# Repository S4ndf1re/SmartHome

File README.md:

# SmartHome

During Covid-19 lockdown, I started a hobby project to experiment with plugin support for MQTT Services.
This repository is the result.

Primarily, this project connected MQTT connections and web UI components with plugins written in Java / Kotlin.

To tests the projects validity, an automatic doorlock opener was developed. This doorlock plugin registered into the plugin systems,
exposed its functionality over Websockets and normal HTTP Endpoints, and communicated over MQTT with two ESP8266, one responsible for reading chips, one for actuating the doorlock mechanism.

For roughly one year, this tool in actual use, until [Smart Home V2](https://github.com/S4ndf1re/SmartHomeV2) was developed as its replacement, due to repeating issues with the Eclipse MQTT Client Library.

# Dependencies

- [HiveMQ MQTT Broker community edition](https://github.com/hivemq/hivemq-community-edition)
- [Dokka Documentation Tool for Kotlin](https://github.com/Kotlin/dokka)

# Documenting the code

The code can be documented as following:

```
.\gradlew :lib:dokkaHtml
.\gradlew :backend:dokkaHtml
```

# "Installing"

To use this Smarthome tool, you have to do the following:

1. Make sure to have a reachable MySql database (currently, only MySql is supported)
2. Create on database using the sql_script.sql file.
3. Build using .\gradlew :backend:build
4. Put the generated jar from build/libs into ./
5. Create all plugins in the ./plugins folder.
6. Create all controller in the ./controller folder.

# Plugins

There is only one test plugin to check whether your build works. It can be found in plugin_test

# Controller

There is one default http controller. The controller resembles just an API. In order to use it, you should consider
using the Smarthome_frontend repository.

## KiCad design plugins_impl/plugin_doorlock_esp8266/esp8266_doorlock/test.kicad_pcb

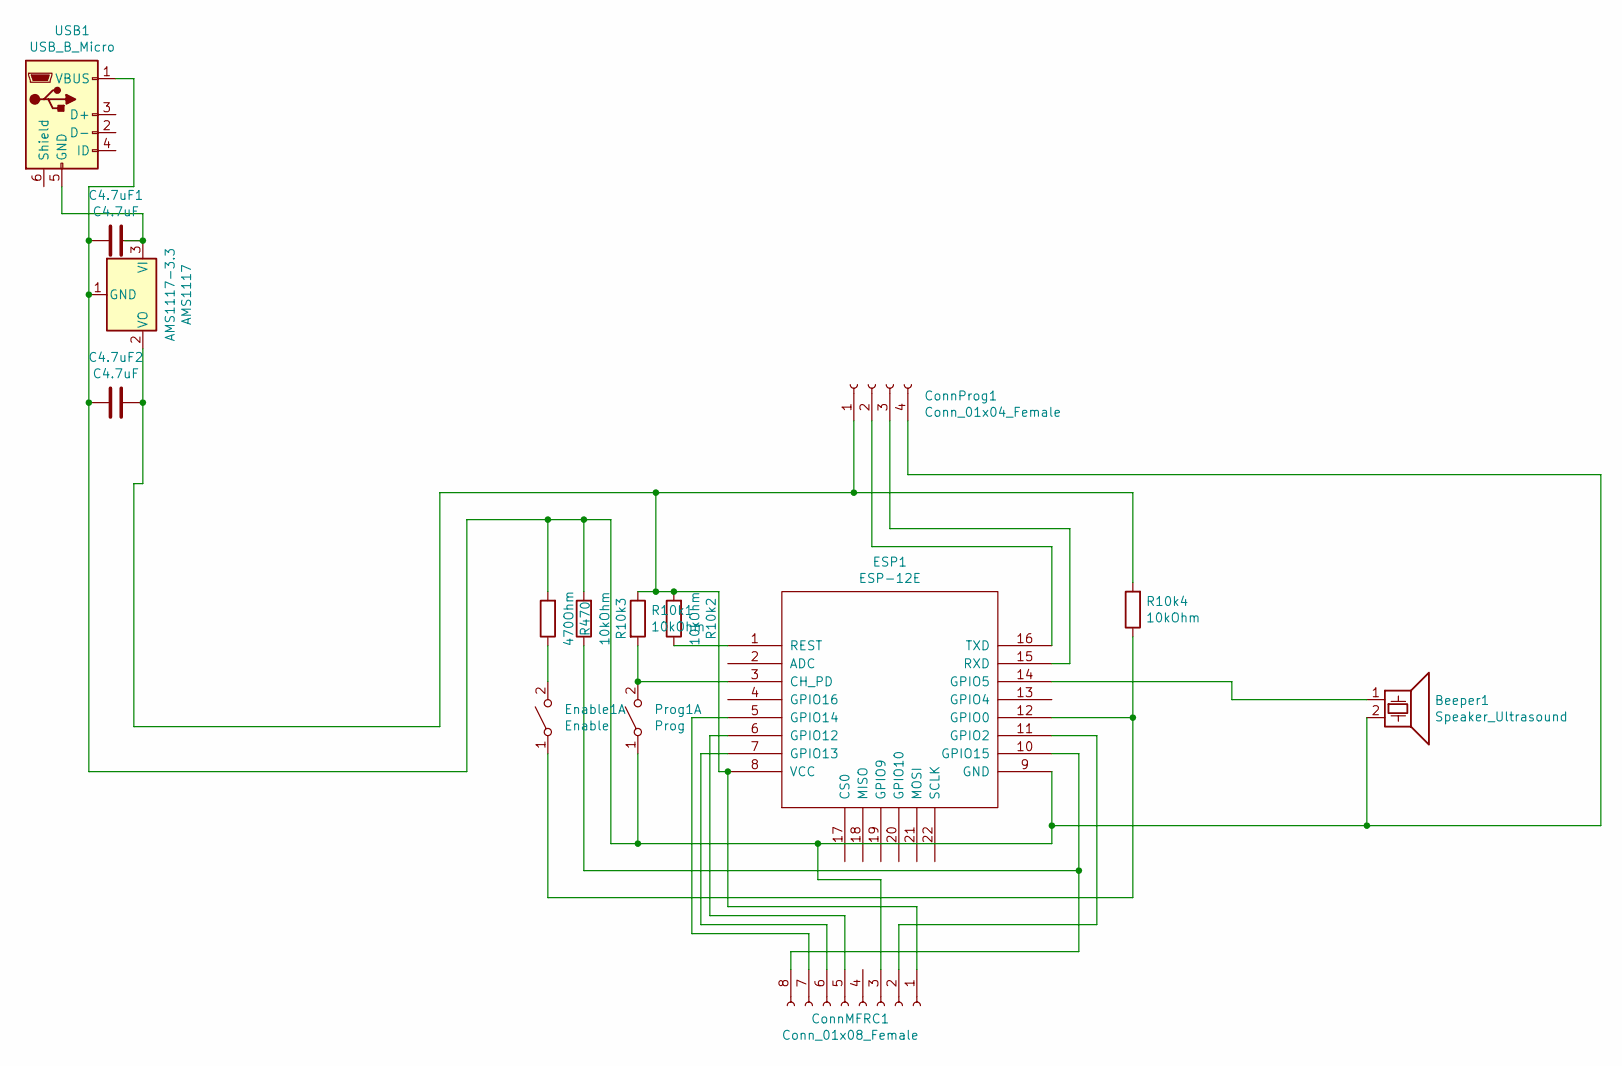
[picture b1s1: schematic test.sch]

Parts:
AMS1117: AMS1117-3.3; SOT-223-3Lead_TabPin2
Beeper1: Speaker_Ultrasound; Buzzer_9mm_6mm
C4.7uF1, C4.7uF2: C4.7uF; CP_Elec_4x5.4
ConnMFRC1: Conn_01x08_Female; MFRC522_PinHeader
ConnProg1: Conn_01x04_Female; TerminalBlock_MetzConnect_Type059_RT06304HBWC_1x04_P3.50mm_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
ESP1: ESP-12E; esp12f
Enable1: Enable; Button
Prog1: Prog; Button
R10k1, R10k2, R10k3, R10k4: 10kOhm; R_0805_2012Metric_Pad1.20x1.40mm_HandSolder
R470: 470Ohm; R_0805_2012Metric_Pad1.20x1.40mm_HandSolder
USB1: USB_B_Micro; USB_Micro-B_Molex-105017-0001

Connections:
unnamed: AMS1117.1 (GND), Beeper1.2, C4.7uF1.2, C4.7uF2.2, ConnMFRC1.3, ConnProg1.4, ESP1.9 (GND), Prog1.1 (A), R10k3.2, R470.2, USB1.1 (VBUS)
unnamed: AMS1117.2 (VO), C4.7uF2.1, ConnMFRC1.1, ConnProg1.1, ESP1.8 (VCC), R10k1.1, R10k2.2, R10k4.2
unnamed: AMS1117.3 (VI), C4.7uF1.1, USB1.5 (GND)
unnamed: Beeper1.1, ESP1.14 (GPIO5)
unnamed: ConnMFRC1.2, ESP1.11 (GPIO2)
unnamed: ConnMFRC1.5, ESP1.6 (GPIO12)
unnamed: ConnMFRC1.6, ESP1.7 (GPIO13)
unnamed: ConnMFRC1.7, ESP1.5 (GPIO14)
unnamed: ConnMFRC1.8, ESP1.10 (GPIO15), R10k3.1
unnamed: ConnProg1.2, ESP1.16 (TXD)
unnamed: ConnProg1.3, ESP1.15 (RXD)
unnamed: ESP1.1 (REST), R10k2.1
unnamed: ESP1.3 (CH_PD), Prog1.2 (B), R10k1.2
unnamed: ESP1.12 (GPIO0), Enable1.1 (A), R10k4.1
unnamed: Enable1.2 (B), R470.1

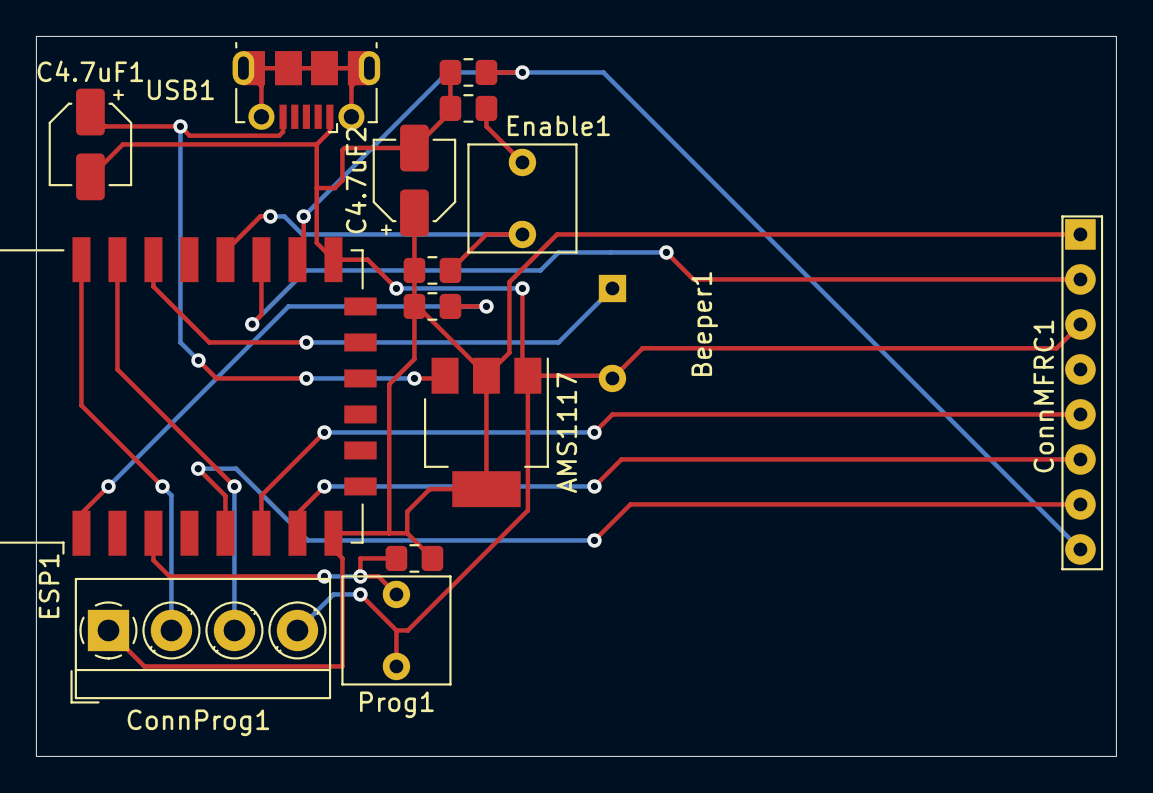
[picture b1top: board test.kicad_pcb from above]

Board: 2 copper layers, 60.0 x 40.0 mm, 15 parts (0 on the bottom side), 15 nets.

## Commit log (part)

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2021-03-29 Added Primitive Plugin System.
2021-03-29 Advancements in plugin system
2021-03-29 Namechange
2021-03-29 Test
2021-03-29 Test2
2021-03-29 Changed Readme
2021-03-30 Adding Doc
2021-03-30 Changes: + More Doc (see build/dokka/index.html + ExtensionLoader<T> Class for extensions + IPlugin enhancement
2021-03-31 Changes to file structure.
2021-03-31 Added basic config.xml with parser in module :backend
2021-04-03 Plugin Subscription Model with plugin.xml files
2021-04-03 Changing of ExtensionLoader<T> because of changes in PluginSystem from previous commit
2021-04-04 Advancements in PluginSystem. Added more generic plugin creation in order to start implementing the Controller functionality
2021-04-05 Added basic GUI elements. Things that have to be considered in the near future: 1. Porting this project to kotlin multiplatform, or creating a new repo 2. What widgets must be added, in order to func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
2021-04-06 Added Image GUI elements. Added Data GUI elements. Added ColorField GUI elements. Things that have to be considered in the near future: 1. Porting this project to kotlin multiplatform, or creating a 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
    TODO:
    InputFields
    TextFields
2021-04-08 Added Image GUI elements. Added Data GUI elements. Added ColorField GUI elements. Things that have to be considered in the near future: 1. Porting this project to kotlin multiplatform, or creating a 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
    TODO:
    InputFields (may be just done via Forms)
2021-04-18 Changes: + gui.Form + IController + IController Implementation
2021-04-20 Changes: - Gui to Json (will be added later again) + New Gui functionality to make life easier for the Plugin developers
2021-04-30 Changes: + Bugfix in ExtensionLoader => New names for plugins + Default controller implementation works for Clickables
2021-04-30 Added controller to main branch
2021-05-16 Added new config for sql server connection
2021-05-16 Textfield frontend support
2021-05-16 ContentNegotiation and basic authentication
2021-05-16 Added OnOffState functionality
2021-05-16 New interface for getContainers. Allows plugins to generate more than one container
2021-05-16 Added Exception printing in case of Plugins wont get loaded
2021-05-16 New Controller Jar
2021-05-16 Added Polymorphic OnOffState for Serialization
2021-05-16 New Plugin Jar
2021-05-16 Added test for TextField and OnOffState Checkbox
2021-05-16 Changed app to use new Config
2021-05-16 Changed Checkbox from Clickable to OnOffState
2021-05-16 Authentication and ContentNegotiation added to build.gradle
2021-05-16 Automatically generated files
2021-05-17 Added Database to main function
2021-05-17 Added Database functionality
2021-05-17 README changes
2021-05-19 Some Data changes
2021-06-29 Added Data basic implementation. Not functional.
    Frontend implementation needed
2021-07-22 Update .gitignore
    Removed .idea and .gradle folder
2021-07-22 Update sketch_apr10a.ino
    Added better wifi and mqtt support.
2021-07-25 Update sketch_apr10a.ino
    Added Mifare Read and write.
2021-08-04 Added working write functionality
2021-08-13 Added stuff to .gitignore
2021-08-13 Esp8266 Doorlock system. Init Plugin
2021-08-24 Added check functionality
2021-08-24 Autogenerated files
2021-08-24 Try fixing gitignore
2021-08-24 Fixed .gitignore and added Data
2021-08-24 Tried fixing DokkaHtml
2021-08-25 Ported Frontend into main Project
2021-08-25 Remove gitignore
2021-08-25 Fixed Dokka html
2021-08-25 Completed part of the documentation
2021-08-25 Removed ToJson.kt, because all components that inherit this, already are serializable by kotlinx.serialization
2021-08-28 Fixed Issue #14
2021-08-28 Fixed Issue #17. And finished backend of Doorlock
2021-09-11 Added opener Arduino Script
2021-10-02 Added arduino projects for door lock plugin
2021-10-02 Added github.com/S4ndf1re/Klog as dependencie
2021-10-02 Fixed versioning of gradle dependencies
2021-10-04 Added new logging library.
2021-10-04 Bug Fix
2021-10-04 Bugfix change password.
2021-10-06 Changed to new logger.
2021-10-06 Added log.json to .gitignore
2021-10-06 Change every null to Optional where possible
2021-10-09 Changed Optional to ?.let {}
2021-10-09 Bugfix Data and Working Alert.js/Alert.kt(combined with Data)
2021-10-11 Bugfix Data and code cleanup for Default Plugin
2021-10-11 Added Data to ESP Plugin
2021-10-13 Export all libs into one jar
2021-10-13 Added current jar files
2021-10-14 Changed lib.gui to suspending functions Thread safety is implemented for Data via Mutex.
2021-10-15 Changed data update to newer and better function call
2021-10-15 Added cleanup on error
2021-11-03 Bugfix unauhtorized and 404 not found
2021-11-04 Added Bugfix and watchscript
2021-11-15 Docker-compose and Docker support for frontend and backend
2021-11-20 Added KiCad files for esp8266 soldering design
2021-11-30 Added Better block loop
2021-12-08 Less security. Hopefully working
